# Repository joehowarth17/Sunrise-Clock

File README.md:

# Sunrise-Clock
This is the code for a “sunrise” alarm clock. The alarm can be set from a simple webpage hosted on an ESP8266. Several RGB LED strips slowly light up simulating a sunrise and a seven-segment display displays the current time. The main microcontroller used is a Psoc 4200 prototyping kit which interfaces with a RTC module. An attiny85 is used with some shift registers to control the seven-segment display, and an ESP8226 hosts a webpage to control the clock and update the time.

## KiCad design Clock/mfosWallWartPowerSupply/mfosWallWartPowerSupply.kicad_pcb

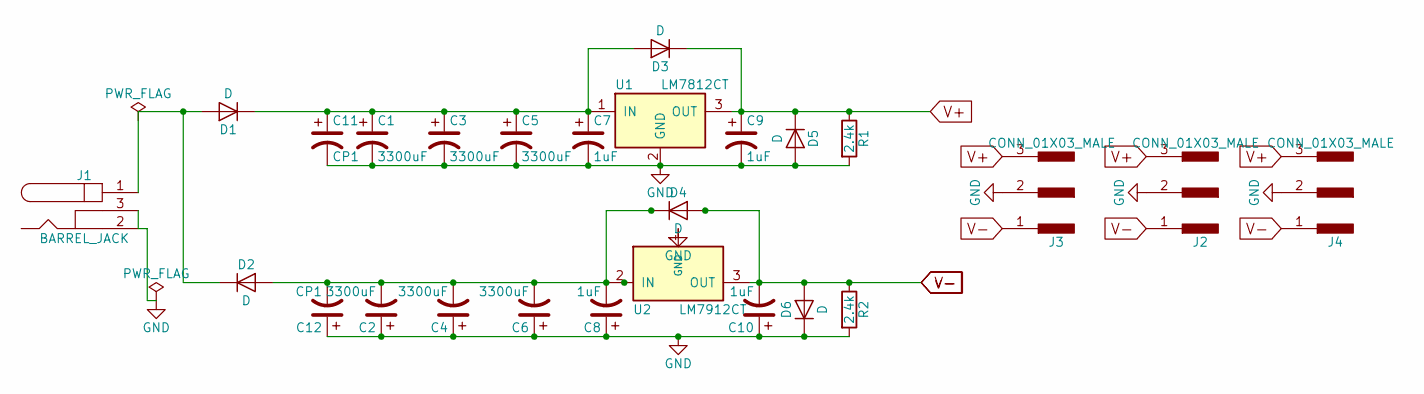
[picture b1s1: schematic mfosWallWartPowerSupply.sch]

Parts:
C1, C2, C3, C4, C5, C6: 3300uF; CP_Radial_D18.0mm_P7.50mm
C7, C8, C9, C10: 1uF; CP_Radial_Tantal_D4.5mm_P2.50mm
C11, C12: CP1; CP_Radial_D18.0mm_P7.50mm
D1, D2, D3, D4, D5, D6: D; D_DO-41_SOD81_P10.16mm_Horizontal
J1: BARREL_JACK
J2, J3, J4: CONN_01X03_MALE; PINHEAD1-3
R1, R2: 2.4k; R_Axial_DIN0207_L6.3mm_D2.5mm_P7.62mm_Horizontal
U1: LM7812CT; TO-220_Vertical
U2: LM7912CT; TO-220_Vertical

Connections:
GND: C1.2, C2.1, C3.2, C4.1, C5.2, C6.1, C7.2, C8.1, C9.2, C10.1, C11.2, C12.1, D5.2 (A), D6.1 (K), J1.2, J1.3, J2.2, J3.2, J4.2, R1.2, R2.2, U1.2 (GND), U2.1 (GND)
unnamed: C1.1, C3.1, C5.1, C7.1, C11.1, D1.1 (K), D3.2 (A), U1.1 (IN)
unnamed: C2.2, C4.2, C6.2, C8.2, C12.2, D2.2 (A), D4.1 (K), U2.2 (IN)
unnamed: D1.2 (A), D2.1 (K), J1.1
V+: C9.1, D3.1 (K), D5.1 (K), J2.3, J3.3, J4.3, R1.1, U1.3 (OUT)
V-: C10.2, D4.2 (A), D6.2 (A), J2.1, J3.1, J4.1, R2.1, U2.3 (OUT)

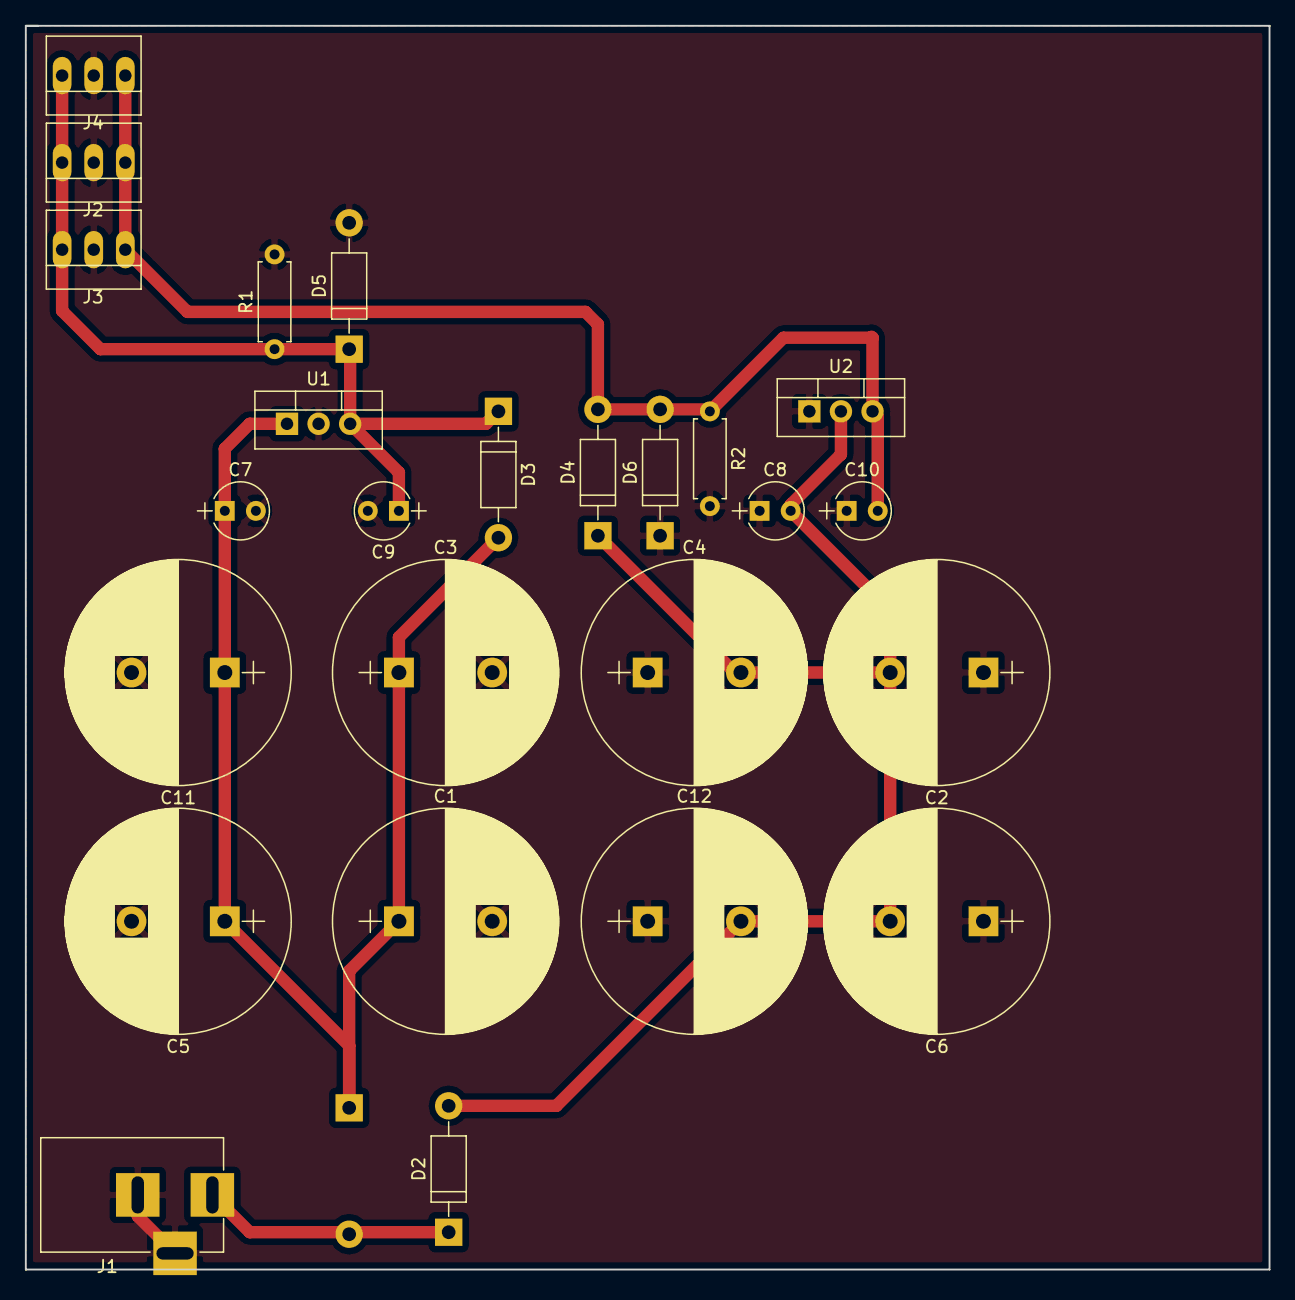
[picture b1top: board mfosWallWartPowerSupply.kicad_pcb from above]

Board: 2 copper layers, 100.0 x 100.0 mm, 26 parts (1 on the bottom side), 6 nets.

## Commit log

2017-02-24 Arduino sketch to test shift registers and led clock display
2017-02-24 started schematic/simulation for led display
2017-02-24 Added transistor and resistor to common gnd
2017-02-25 Added pdf with led display pin mapping
2017-02-25 added py script and spreadsheet
2017-03-07 psoc main function
    shift out function not tested
2017-05-11 add everything
2017-06-20 Added Esp8266 Neopixel program
2017-08-09 Got rid of junk, added psoc firmware.
2017-08-12 changed esp8266 to use get and post requests
2017-08-23 now updatees time from tnp server.
2018-01-07 Removed old files.
2018-01-07 Removed serial log files.
2018-01-07 ESP8266 working version. Please enter the commit message for your changes. Lines starting
2018-01-07 Update Esp8266_Neopixel_V2.ino
    Fixed typos and added some comments.
2018-01-07 Psoc working version.
2018-01-29 Rename setAlarm to setAlarm.html
2018-01-29 Rename setColor to setColor.html
